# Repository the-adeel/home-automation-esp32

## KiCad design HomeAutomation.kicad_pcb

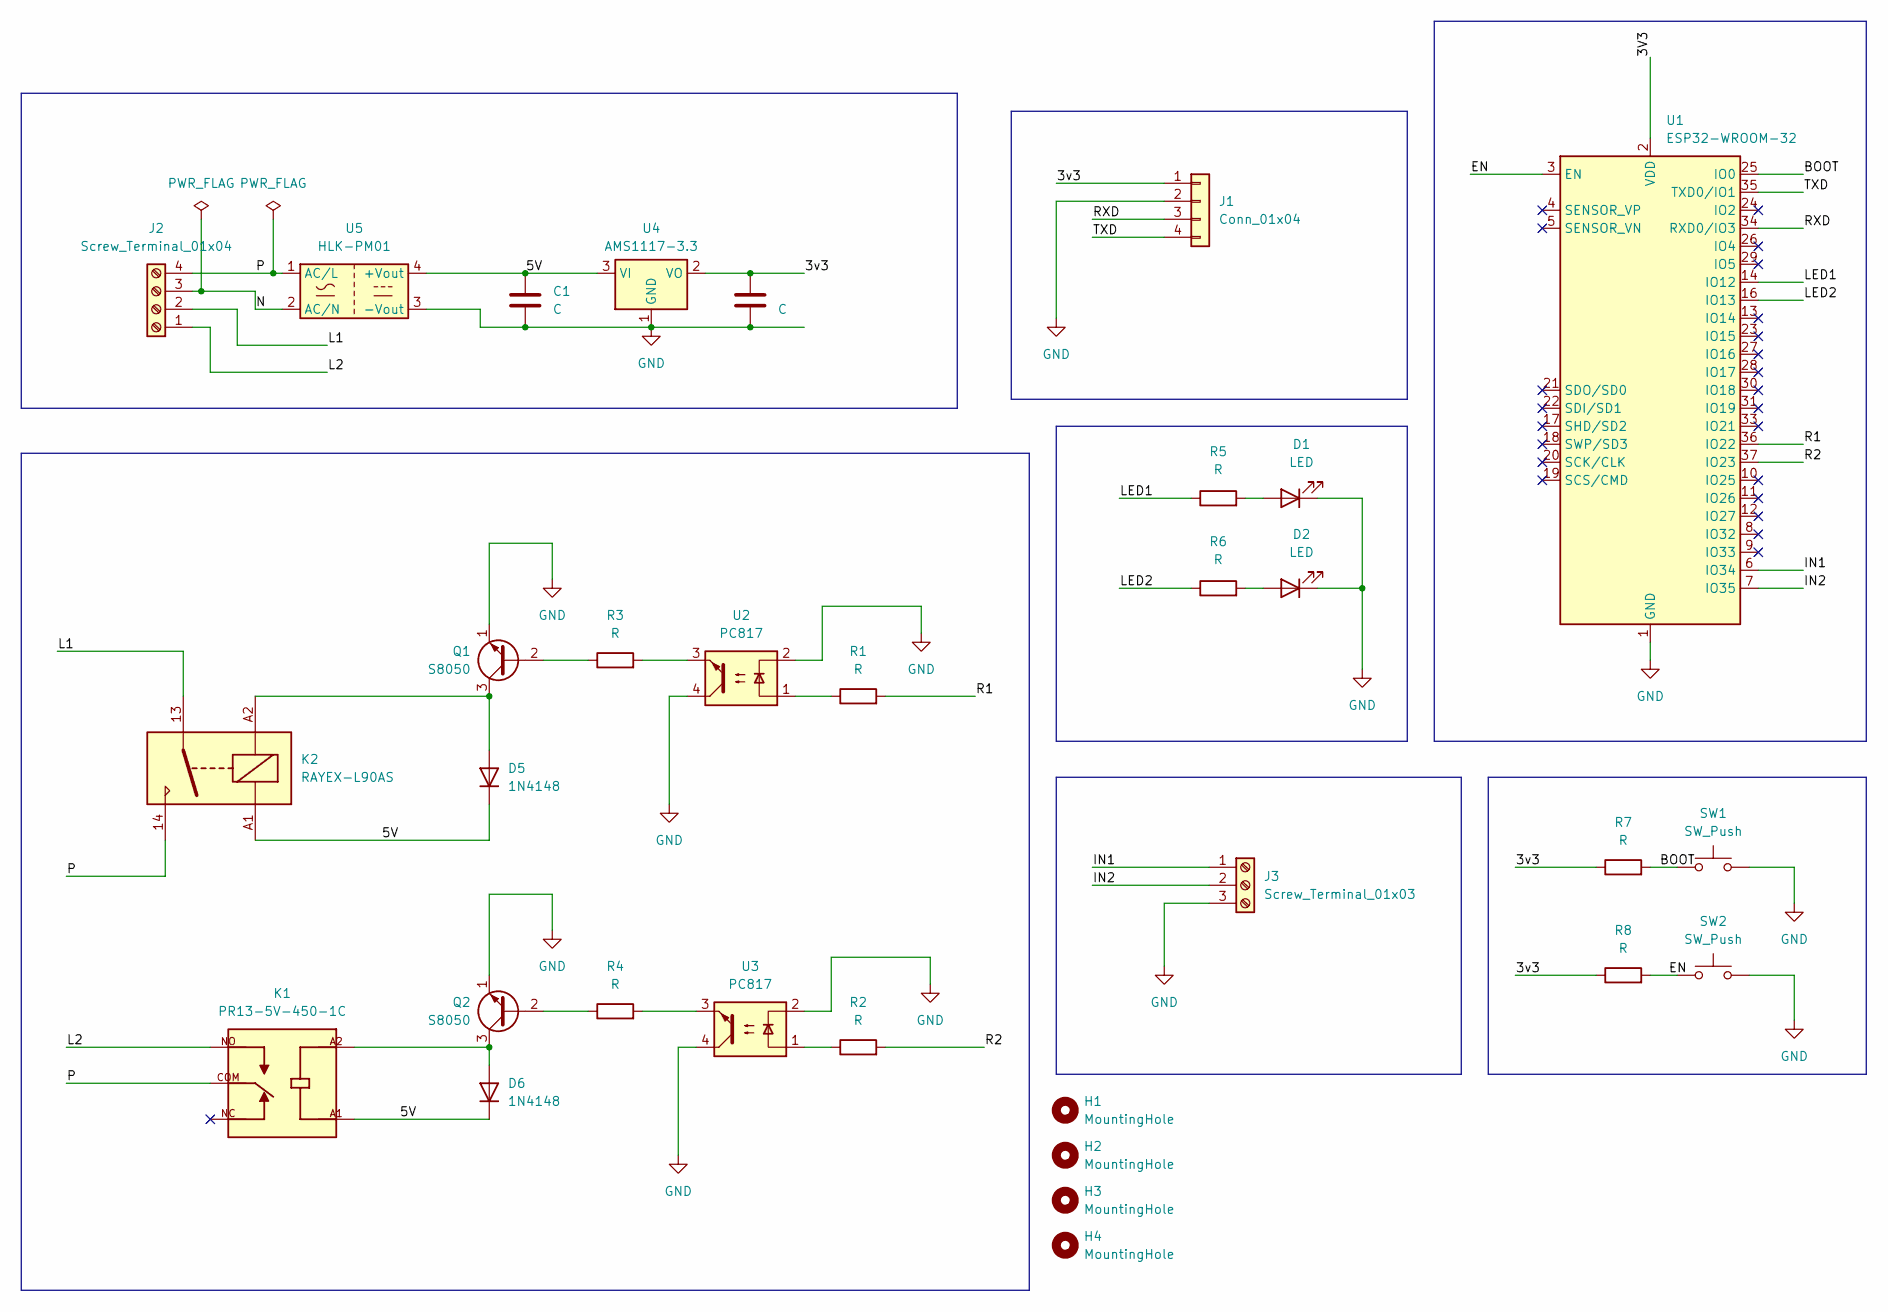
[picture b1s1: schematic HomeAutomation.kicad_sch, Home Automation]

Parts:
C1, C2: C; C_0805_2012Metric
D1, D2: LED; LED_0805_2012Metric
D5, D6: 1N4148; D_DO-35_SOD27_P7.62mm_Horizontal
H1, H2, H3, H4: MountingHole; MountingHole_2.7mm_M2.5_Pad_Via
J1: Conn_01x04; PinHeader_1x04_P2.54mm_Vertical
J2: Screw_Terminal_01x04; TerminalBlock_MaiXu_MX126-5.0-04P_1x04_P5.00mm
J3: Screw_Terminal_01x03; TerminalBlock_MaiXu_MX126-5.0-03P_1x03_P5.00mm
K1: PR13-5V-450-1C; RELAY_PR13-5V-450-1C; PARTREV 1.0
K2: RAYEX-L90AS; Relay_SPST_RAYEX-L90AS
Q1, Q2: S8050; TO-92_Inline
R1, R2, R3, R4, R5, R6, R7, R8: R; R_0805_2012Metric
SW1, SW2: SW_Push; SW_PUSH_6mm
U1: ESP32-WROOM-32
U2, U3: PC817; DIP-4_W7.62mm
U4: AMS1117-3.3; SOT-223-3_TabPin2
U5: HLK-PM01; Converter_ACDC_Hi-Link_HLK-PMxx

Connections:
/3V3: U1.2 (VDD)
/3v3: C2.1, J1.1, R7.1, R8.1, U4.2 (VO)
/5V: C1.1, D5.1 (K), D6.1 (K), K1.A1, K2.A1, U4.3 (VI), U5.4 (+Vout)
/BOOT: R7.2, SW1.1, U1.25 (IO0)
/EN: R8.2, SW2.1, U1.3 (EN)
/IN1: J3.1, U1.6 (IO34)
/IN2: J3.2, U1.7 (IO35)
/L1: J2.2, K2.13
/L2: J2.1, K1.NO
/LED1: R5.1, U1.14 (IO12)
/LED2: R6.1, U1.16 (IO13)
/N: J2.3, U5.2 (AC/N)
/P: J2.4, K1.COM, K2.14, U5.1 (AC/L)
/R1: R1.2, U1.36 (IO22)
/R2: R2.2, U1.37 (IO23)
/RXD: J1.3, U1.34 (RXD0/IO3)
/TXD: J1.4, U1.35 (TXD0/IO1)
GND: C1.2, C2.2, D1.1 (K), D2.1 (K), J1.2, J3.3, Q1.1 (E), Q2.1 (E), SW1.2, SW2.2, U1.1 (GND), U1.15 (GND), U1.38 (GND), U1.39 (GND), U2.2, U2.4, U3.2, U3.4, U4.1 (GND), U5.3 (-Vout)
unnamed: D1.2 (A), R5.2
unnamed: D2.2 (A), R6.2
unnamed: D5.2 (A), K2.A2, Q1.3 (C)
unnamed: D6.2 (A), K1.A2, Q2.3 (C)
unnamed: Q1.2 (B), R3.1
unnamed: Q2.2 (B), R4.1
unnamed: R1.1, U2.1
unnamed: R2.1, U3.1
unnamed: R3.2, U2.3
unnamed: R4.2, U3.3

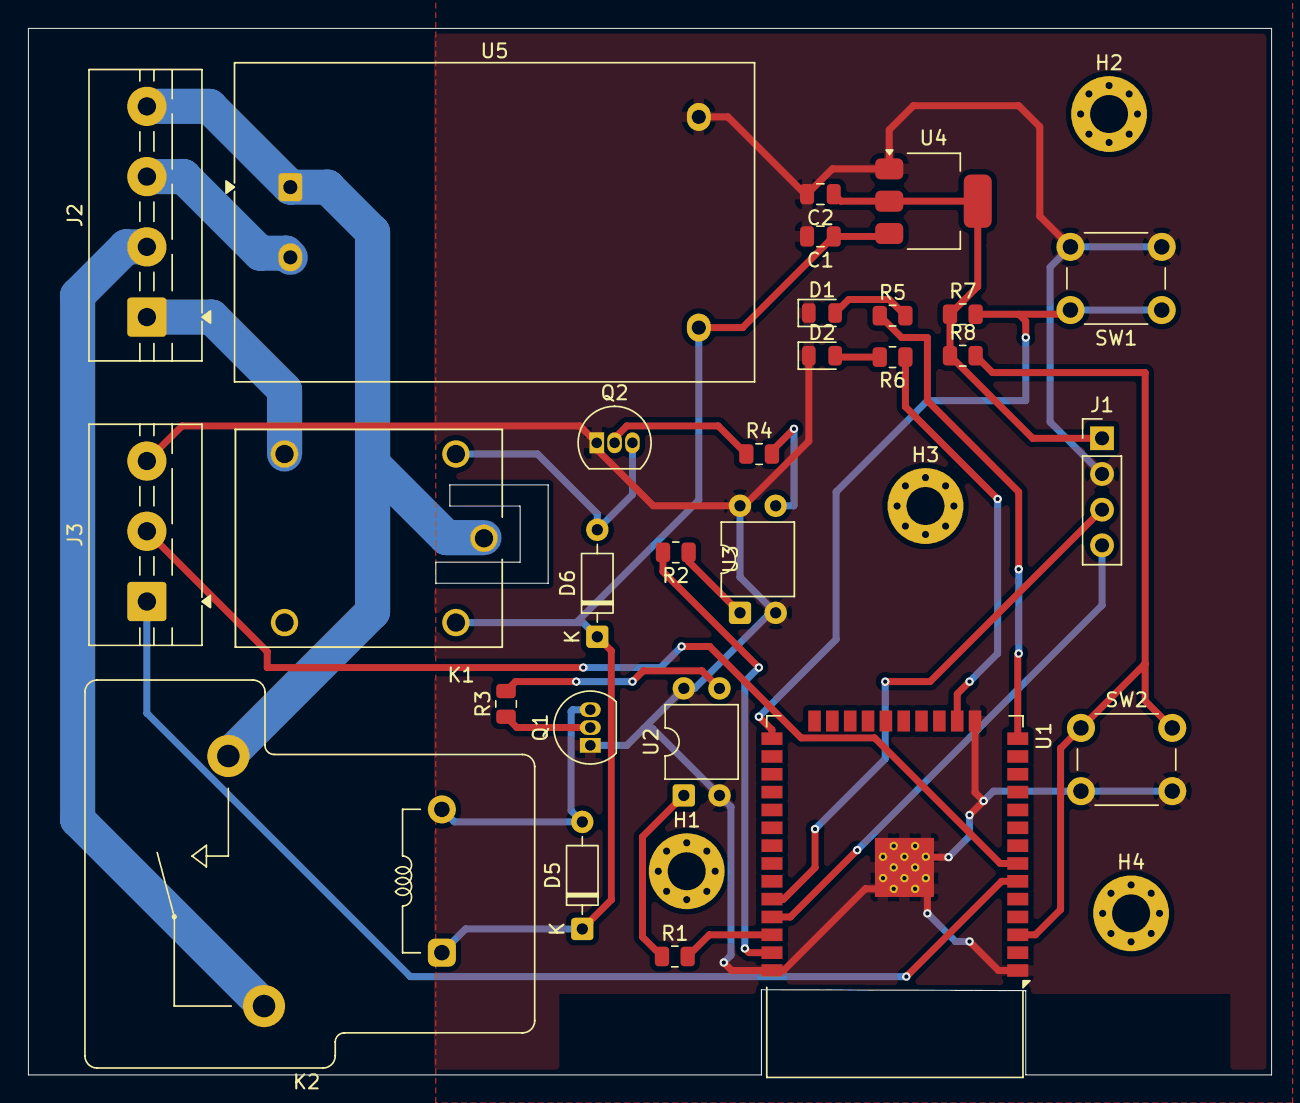
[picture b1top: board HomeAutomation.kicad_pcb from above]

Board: 2 copper layers, 88.5 x 74.5 mm, 32 parts (0 on the bottom side), 27 nets.
